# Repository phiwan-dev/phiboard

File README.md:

# phiboard
in progress, currently in the prototype phase...

# Third-Party Assets
### KiCad Symbols
The following Assets are from a third-party. Their original license still applies.
- Altium ISP1807-LR symbol in [`board/libraries/ISP1807-LR_Footprint.SchLib`](board/libraries/ISP1807-LR_Footprint.SchLib)
from the [manufacturers website](https://www.insightsip.com/products/bluetooth-le-modules/isp1807). There is no mention of a license.
- Kicad ISP1807-edit symbol in [`board/libraries/nordic-lib-kicad-isp1807.kicad_sym`](board/libraries/nordic-lib-kicad-isp1807.kicad_sym)
modified but based on the manufacturers symbol. Modifications follow this projects license (CERN-OHL-P-2.0).
- Kicad Nordic PMIC symbols in [`board/libraries/nordic-lib-kicad-npm.kicad_sym`](board/libraries/nordic-lib-kicad-npm.kicad_sym)
from https://github.com/hlord2000/nordic-lib-kicad using the CERN-OHL-P-2.0 license.
### KiCad Footprints
- Altium ISP1807-LR footprint in [`board/libraries/ISP1807-LR_Footprint.PcbLib`](board/libraries/ISP1807-LR_Footprint.PcbLib)
from the [manufacturers website](https://www.insightsip.com/products/bluetooth-le-modules/isp1807). There is no mention of a license.
- Kicad ISP1807-edit footprint in [`board/libraries/nordic-lib-kicad-isp1807.pretty`](board/libraries/nordic-lib-kicad-isp1807.pretty)
modified but based on the manufacturers symbol. Modifications follow this projects license (CERN-OHL-P-2.0).

<!-- ## Goals -->
<!-- - fully reversible pcb including hotswap sockets, MCU, OLED screen -->
<!-- - wireless using the XIAO BLE as MCU -->
<!-- - low profile (choc kailh) and thin PCB + components -->
<!-- - no visible screws from the top -->
<!-- - no visible seams from the top -->
<!-- - custom graphics and silk screen -->
<!-- - super easy, local zmk development -->

<!-- # Manual additions after Ergogen -->
<!-- Ergogen is used to generate most parts of the PCB. From within the ergogen folder, this can be done using: -->
<!-- ``` -->
<!-- ergogen . && cp output/pcbs/pcb.kicad_pcb ../kicad-prj/ -->
<!-- ``` -->
<!-- However, various smaller modifications as well as the reversible OLED and silkscreen graphics are placed manually by hand. -->
<!-- It is likely that this could be done through ergogen as well, feel free to fork and adjust my config. -->
<!-- All modifications are listed in here: -->
<!-- - Removed silksceens from diodes and modified silksceen for the battery pads. Be careful with this, as it make messing up the diode configuration very easy! -->
<!-- - Wired up MCU and keys in a reversible fashion -->
<!-- - Included reversible OLED --> 
<!-- - Put on silkscreens on front [`porsche-front-big.kicad_mod`](./kicad-prj/graphics.pretty/porsche-front-big.kicad_mod) and back [`porsche-back-big.kicad_mod`](./kicad-prj/graphics.pretty/porsche-back-big.kicad_mod) -->

<!-- # Customize Graphics -->
<!-- In [graphics](./kicad-prj/graphics/) you can find the source images used in this project. -->
<!-- There are two types of graphics. -->
<!-- ### Silkscreen -->
<!-- The silksceen uses the porsche images. -->
<!-- To use a different image you have to open `kicad > image converter`. -->
<!-- In here you can load your desired image, choose an output size and threshold and save it as footprint on F.Silkscreen. -->
<!-- In order for KiCad to detect your custom footprints, you have to save them to a folder with the extension `.pretty` like in [`kicad-prj/graphics.pretty/`](./kicad-prj/graphics.pretty/). -->
<!-- Lastly you need to tell KiCad where to find your footprints. -->
<!-- If you decide to use my project and its `graphics.pretty` folder then KiCad should automatically pick it up through the `fp-lib-table`. -->
<!-- Else, you can specify your `.pretty` path in `Preferences > Manage Footprint Libraries... > Project Specific Libraries`. -->
<!-- ### Solder Images -->
<!-- In the palm of the hand there is a little empty space on the PCB which I decided to use with images which are printed on there using solder. -->
<!-- I got the idea from [this video](https://www.youtube.com/watch?v=ohu4tZ4qov8). -->
<!-- Here is the workflow to put your own images on there: -->
<!-- You will most likely have a .png or .jpg image, which needs to be transformed to .svg. -->
<!-- For this you can use popular online tools like [convertio.co](https://convertio.co/). -->
<!-- Optionally you can try to optimize your svg using [this website](https://optimize.svgomg.net/), although it didn't make much of a difference for me. -->
<!-- Next, we need to transform our svg into an array of points, for which i used [this website](https://shinao.github.io/PathToPoints/). -->
<!-- Lastly, you can replace the point array in [`ergogen/footprints/phi-caps`](./ergogen/footprints/phi-caps.js) for the front side or [`ergogen/footprints/phi-logo`](./ergogen/footprints/phi-logo.js) for the back side. -->

<!-- # Parts -->
<!-- 40 keys, 20 per side -->
<!-- - 40 choc kailh switches -->
<!-- - 40 choc kailh keycaps -->
<!-- - 40 choc hotswap sockets -->
<!-- - 40 smd diodes 1N4148 -->
<!-- - 2 xiao ble -->
<!-- - 2 oled 0.91 inch i2c (optional) -->
<!-- - 2 batteries 3.7v (optional, requres cable otherwise) -->

<!-- # Firmware -->
<!-- Usually ZMK is compiled throug a GitHub actions workflow. However, I prefer to use it locally using a docker devcontainer. The devcontainer is provided by the official ZMK project. -->

<!-- ## Setting up the ZMK docker toolchain -->
<!-- ```bash -->
<!-- nix develop     # or install devcontainer cli otherwise -->
<!-- cd <path-to-phiboard>/firmware -->
<!-- ./setup-zmk.sh  # this may take a while -->
<!-- ``` -->

<!-- ## Compiling the ZMK firmware -->
<!-- ```bash -->
<!-- nix develop     # or install devcontainer cli otherwise -->
<!-- cd <path-to-phiboard>/firmware -->
<!-- ./build.sh  # clean build, is needed the first time -->
<!-- ./build.sh --cached   # faster, if a build has been done before -->
<!-- # the firmware is now located at <path-to-phiboard>/firmware/(left|right).uf2 -->
<!-- ``` -->

<!-- ## Flashing the firmware -->
<!-- - connect mcu with pc -->
<!-- - double press the reset button -->
<!-- - the file explorer should now show a usb media -->
<!-- - copy the corresponding .uf2 firmware to the usb media -->
<!-- - it should now auto-eject and run the new firmware -->

<!-- ## Fighting with ZMK -->
<!-- - spend a lot of time on local toolchain and scripts -->
<!-- - other projects may have their config files in different places -->
<!-- - explain most important files which the user might want to change (and where) -->
<!-- - confusing, overwhelming (at first) -->
<!-- - flash reset firmware to fix problems -->
<!-- - dtsi is "weird" because of the way the matrix is connected (only on prototype) -->
<!-- - right overlay columns are reversed because its mirrored but pcb is non-mirrored -->
<!-- - main half controls layers of secondary half -> perhaps need to flash both sides for keymap to take new changes -->
<!-- - displays have close to 0 documentation at all -->

<!-- # Soldering -->
<!-- - watch a solder intro video if you dont know what you are doing -->
<!-- - the second half will be better -->
<!-- - put solder on the pads, then heat the pads and press components in -->
<!-- - if possible, test connectivity from mcu to front pads -->
<!-- - care for diode direction (on prototype) -->

<!-- # Future fixes (from prototype) -->
<!-- - key spacing? -->
<!-- - different display -->

<!-- # Thanks -->
<!-- - to https://github.com/MvEerd/ergogen/tree/mveerd for ergogen -->
<!-- - to https://flatfootfox.com/ergogen-introduction/ for teaching ergogen -->
<!-- - to https://github.com/Pipshag/goosekb for inspiration on ergogen and zmk -->
<!-- - to https://www.youtube.com/watch?v=ohu4tZ4qov8 for finally making me follow through -->
<!-- - and many, many more! -->

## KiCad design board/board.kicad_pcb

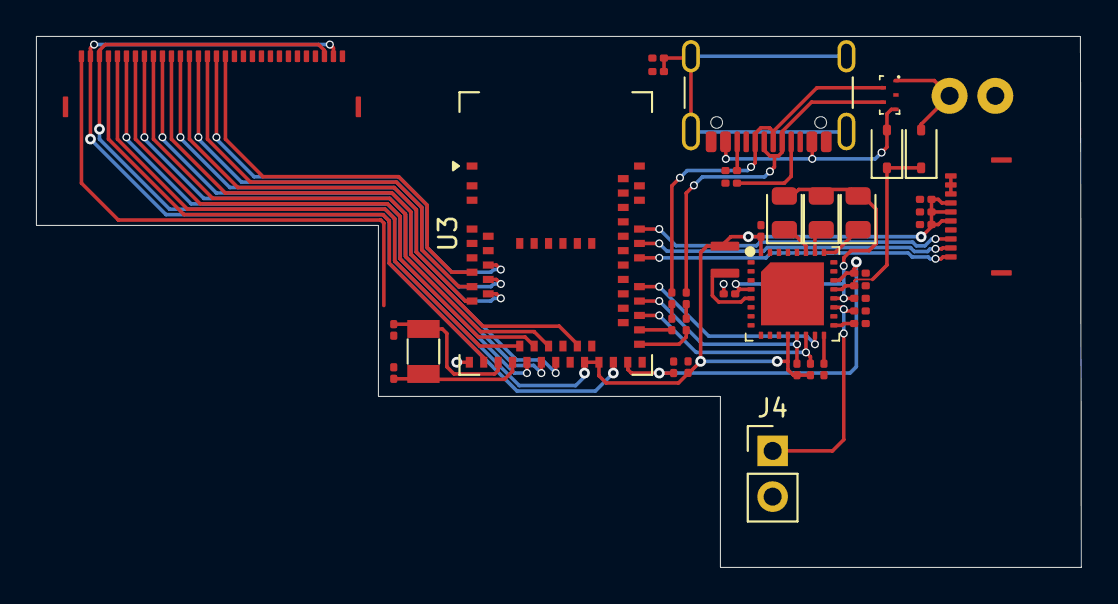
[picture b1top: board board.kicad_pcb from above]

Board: 2 copper layers, 58.1 x 29.5 mm, 41 parts (1 on the bottom side), 55 nets.

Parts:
C2: 10nF; C_0201_0603Metric
C3, C4, C12, C14: 1uF; C_0201_0603Metric
C6: 470pF; C_0201_0603Metric
C7, C8: 12.5pF; C_0201_0603Metric
C9, C10, C15, C16, C17: 10uF; C_0201_0603Metric
C13: 2.2uF; C_0201_0603Metric
D3, D4: D_Schottky; D_SOD-323
D6, D7, D8: LED; LED_0805_2012Metric
J2: Conn_01x10; THD_0510-10CL-GF
J3: Conn_01x06; swd_pad
J4: Conn_01x02; PinHeader_1x02_P2.54mm_Vertical
J7: Conn_01x30; THD_0510-30CL-GF
J8: USB_C_Receptacle_USB2.0_16P; USB_C_Receptacle_GCT_USB4105-xx-A_16P_TopMnt_Horizontal
J9: Conn_01x02; magnetic connector 01x02P
L1: 2.2uH; L_0806_2016Metric
R4, R14: 5.1kR; R_0201_0603Metric
R5, R12, R13: 10kR; R_0201_0603Metric
R6, R7, R8, R9: 10R; R_0201_0603Metric
R10: 0R; R_0201_0603Metric
R11: 250-500kR; R_0201_0603Metric
U2: nPM1300-QEAA; nordic_npm1300-QEAA_qfn
U3: MDBT50Q-P1MV2; Raytac_MDBT50Q
U4: TVS_Array; DFN2010
Y1: 32k Hz; Crystal_SMD_3215-2Pin_3.2x1.5mm

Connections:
+1V8: J7.2, J7.29, U3.31 (DCCH)
+3V3: C3.1, C4.1, C6.1, C10.2, C17.1, J2.5, J2.6, J2.7, J3.2, J7.3, J7.28, L1.2, R12.1, R13.1, U2.12 (VDDIO), U2.32 (VOUT2), U3.28 (VDD), U3.30 (VDDH)
GND: C2.1, C3.2, C4.2, C6.2, C7.2, C8.2, C9.2, C10.1, C12.1, C13.2, C14.2, C15.2, C16.2, C17.2, J2.4, J2.8, J2.9, J2.10, J3.6, J4.2, J7.1, J7.30, J8.A1 (GND), J8.A12 (GND), J8.B1 (GND), J8.B12 (GND), J9.2, R4.1, R5.1, R10.1, R11.1, R14.1, U2.6 (PVSS2), U2.18 (NTC), U2.33 (AVSS), U3.1 (GND), U3.2 (GND), U3.15 (GND), U3.33 (GND), U3.55 (GND), U4.2 (GND)
unnamed: D3.2 (A), J8.A4 (VBUS), J8.A9 (VBUS), J8.B4 (VBUS), J8.B9 (VBUS), U4.3
unnamed: D4.2 (A), J9.1, U4.1
unnamed: D6.1 (K), U2.25 (LED0)
unnamed: D7.1 (K), U2.26 (LED1)
unnamed: D8.1 (K), U2.27 (LED2)
unnamed: J8.A5 (CC1), R4.2
unnamed: J8.B5 (CC2), R14.2
unnamed: C2.2, J8.S1 (SHIELD), R5.2
unnamed: R6.1, R7.2
unnamed: R8.1, R9.2
unnamed: L1.1, U2.5 (SW2)
unnamed: R10.2, U2.17 (VSET1)
unnamed: R11.2, U2.16 (VSET2)
unnamed: R8.2, U3.35 (D+)
unnamed: R6.2, U3.34 (D-)
unnamed: C8.1, U3.17 (P0.00), Y1.1
unnamed: C7.1, U3.18 (P0.01), Y1.2
key1: J7.4, U3.16 (P0.27)
key2: J7.5, U3.19 (P0.26)
key3: J7.6, U3.20 (P0.04)
key4: J7.7, U3.21 (P0.05)
key5: J7.8, U3.22 (P0.06)
key6: J7.9, U3.23 (P0.07)
key7: J7.10, U3.24 (P0.08)
key8: J7.11, U3.27 (P0.11)
key9: J7.12, U3.13 (P0.28)
key10: J7.13, U3.14 (P0.30)
key11: J7.14, U3.11 (P0.02)
key12: J7.15, U3.12 (P0.31)
key13: J7.16, U3.9 (P0.03)
key14: J7.17, U3.10 (P0.29)
key18: J7.21, U3.42 (P0.19)
key19: J7.22, U3.43 (P0.21)
key20: J7.23, U3.45 (P0.23)
key21: J7.24, U3.49 (P0.25)
key22: J7.25, U3.52 (P0.09)
key23: J7.26, U3.54 (P0.10)
nreset: J3.5, U3.40 (P0.18)
scl: R13.2, U2.14 (SCL), U3.37 (P0.13)
sclk: J2.1, U3.44 (P0.20)
scs: J2.3, U3.48 (P0.24)
sda: R12.2, U2.13 (SDA), U3.39 (P0.15)
shphld: U2.15 (SHPHLD), U3.41 (P0.17)
si: J2.2, U3.46 (P0.22)
swd_clk: J3.4, U3.53 (SWDCLK)
swd_data: J3.3, U3.51 (SWDIO)
usbd+: J8.A6 (D+), J8.B6 (D+), R9.1, U4.5
usbd-: J8.A7 (D-), J8.B7 (D-), R7.1, U4.4
vbat: C13.1, J4.1, U2.19 (VBAT)
vbus: C9.1, C14.1, U2.22 (VBUSOUT), U3.32 (VBUS)
vbus_raw: C12.2, D3.1 (K), D4.1 (K), U2.21 (VBUS)
vsys: C15.1, C16.1, D6.2 (A), D7.2 (A), D8.2 (A), U2.4 (PVDD), U2.20 (VSYS)

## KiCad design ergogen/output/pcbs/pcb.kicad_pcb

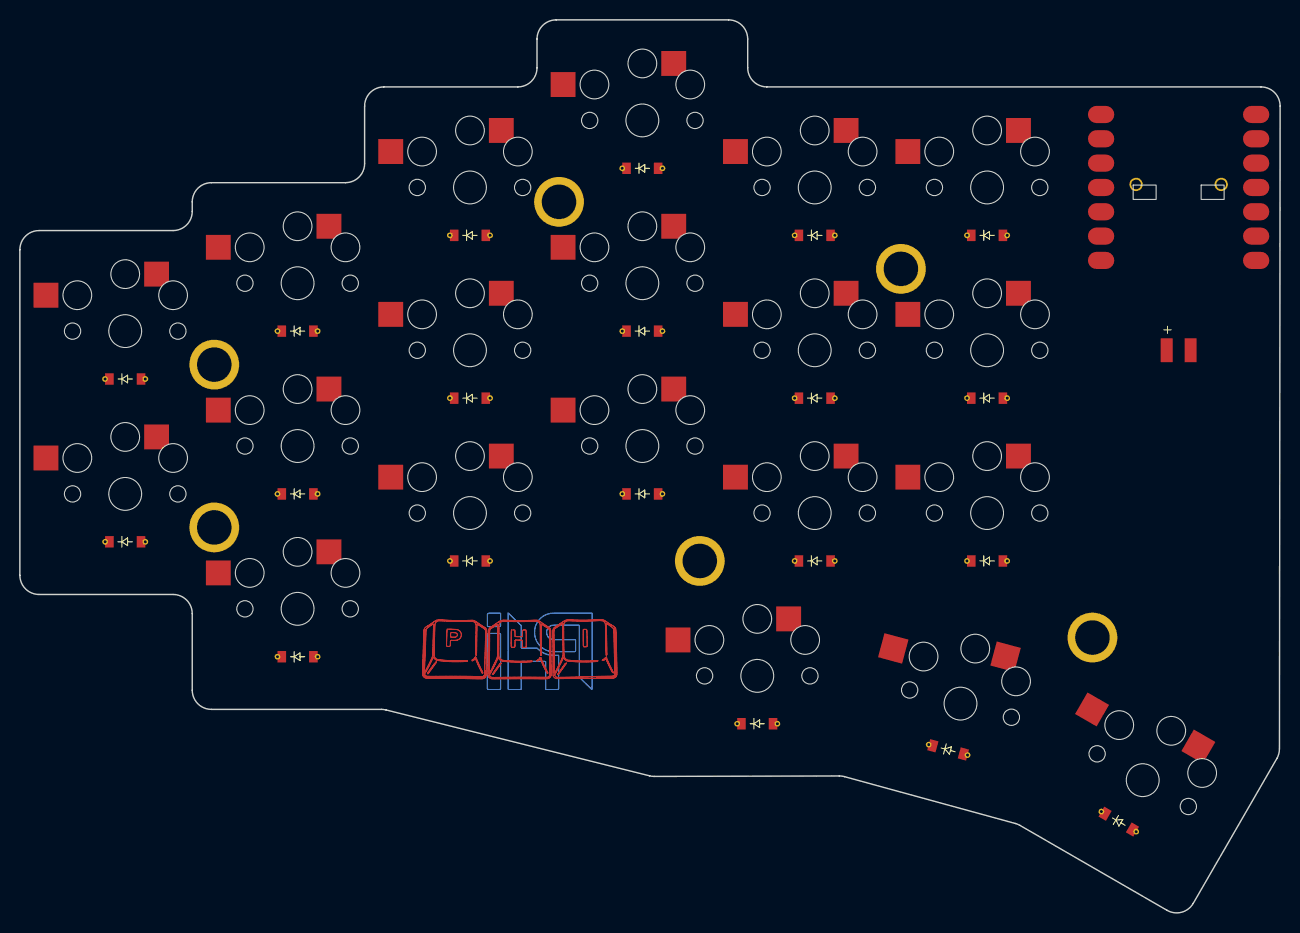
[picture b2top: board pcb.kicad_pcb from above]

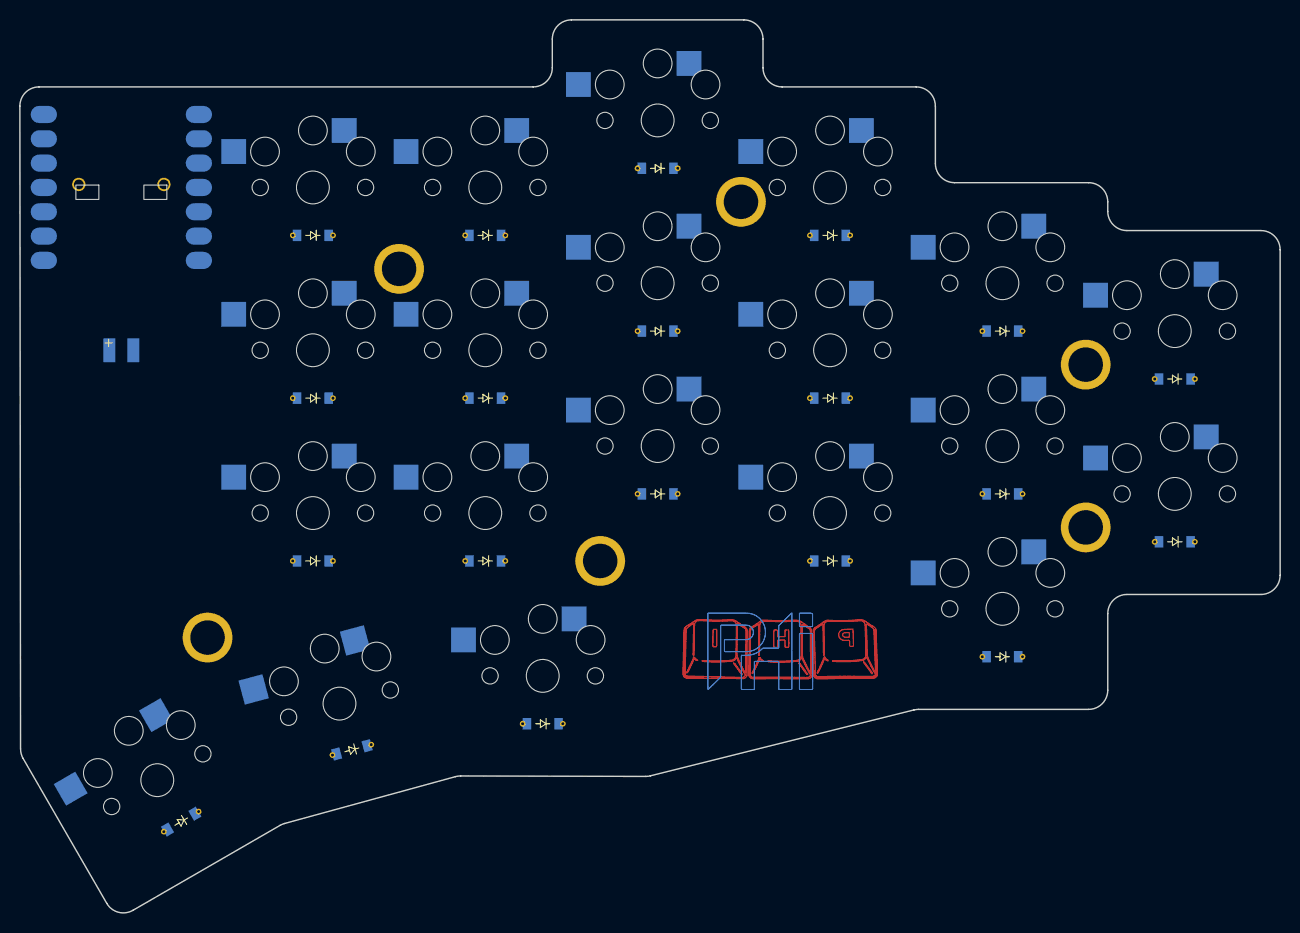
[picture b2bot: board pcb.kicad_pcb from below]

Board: 2 copper layers, 131.6 x 93.2 mm, 48 parts (20 on the bottom side), 31 nets, no tracks yet.

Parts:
Di1, Di2, Di3, Di4, Di5, Di6, Di7, Di8, Di9, Di10, Di11, Di12, Di13, Di14, Di15, Di16, Di17, Di18, Di19, Di20: D_SOD-123
H1, H2, H3, H4, H5, H6: mounting_hole
MCU1: xiao-ble-smd-reversible
PAD1: pads
S1, S2, S3, S4, S5, S6, S7, S8, S9, S10, S11, S12, S13, S14, S15, S16, S17, S18, S19, S20: PG1350

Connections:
BAT+: MCU1.19, PAD1.1, PAD1.2
GND: MCU1.13, PAD1.1, PAD1.2
cindex: MCU1.8, S12.1, S13.1, S14.1, S19.1
cinner: MCU1.7, S15.1, S16.1, S17.1, S20.1
cmiddle: MCU1.9, S9.1, S10.1, S11.1, S18.1
cpinky: MCU1.11, S2.1, S3.1, S4.1, S5.1
cring: MCU1.10, S1.1, S6.1, S7.1, S8.1
index_bottom: Di12.2, S12.2
index_home: Di13.2, S13.2
index_top: Di14.2, S14.2
inner_bottom: Di15.2, S15.2
inner_home: Di16.2, S16.2
inner_top: Di17.2, S17.2
left_cluster: Di18.2, S18.2
middle_bottom: Di9.2, S9.2
middle_cluster: Di19.2, S19.2
middle_home: Di10.2, S10.2
middle_top: Di11.2, S11.2
outer_home: Di1.2, S1.2
outer_top: Di2.2, S2.2
pinky_bottom: Di3.2, S3.2
pinky_home: Di4.2, S4.2
pinky_top: Di5.2, S5.2
rbottom: Di3.1, Di6.1, Di9.1, Di12.1, Di15.1, MCU1.3
rhome: Di4.1, Di7.1, Di10.1, Di13.1, Di16.1, MCU1.2
right_cluster: Di20.2, S20.2
ring_bottom: Di6.2, S6.2
ring_home: Di7.2, S7.2
ring_top: Di8.2, S8.2
rthumbs: Di1.1, Di2.1, Di18.1, Di19.1, Di20.1, MCU1.4
rtop: Di5.1, Di8.1, Di11.1, Di14.1, Di17.1, MCU1.1

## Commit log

2025-05-23 dev: init
2025-05-23 dev: add units
2025-05-23 dev: add main matrix
2025-05-23 dev: add thumb cluster
2025-06-04 dev: add flake for dev shell
2025-06-04 dev: enable nix-direnv
2025-06-04 dev: add board outline
2025-06-06 dev: add more tooling to flake
2025-06-06 fix: remove mirror attribute in favor of reversable pcb
2025-06-06 dev: add pcb with reverse hotswap choc switches
2025-06-07 dev: add diodes with custom footprint
2025-06-07 dev: add mcu to ble
2025-06-07 dev: add readme with parts list
2025-06-07 dev: add kicad project for pcb editing
2025-06-07 dev: add column and row nets to keys
2025-06-07 dev: add battery pads
2025-06-07 dev: add screw points and mounting points
2025-06-09 dev: add small pcb graphics
2025-06-09 dev: add source graphics used for pcb
2025-06-09 dev: add pcb graphic footprints
2025-06-09 dev: add output files
2025-06-09 dev: remove diode silkscreens
2025-06-09 dev: wired up mcu pads on pcb
2025-06-09 dev: wire up key matrix
2025-06-09 dev: include reversible oled screen
2025-06-10 fix: remove reset cutouts from xiao ble
2025-06-10 dev: add kicad outputs
2025-06-10 fix: update readme
2025-06-10 fix: tidy up config
2025-06-10 dev: add LICENSE
2025-07-11 dev: init zmk files
2025-07-19 dev: add zmk docker tutorial to readme
2025-07-20 fix: restructure project into distinct ergogen, kicad and zmk folders
2025-07-20 fix: use goosekb zmk config as starting point for firmware
2025-07-20 zmk: renamed goose to phiboard
2025-07-20 zmk: remove sensors
2025-07-20 docs: reflect changes in readme
2025-07-20 zmk: add setup script
2025-07-20 zmk: add build script
2025-07-20 docs: add script usage to readme
2025-07-20 fix: rename goose folder to phiwan
2025-07-21 zmk: refine build and setup script
2025-07-21 fix: adapt zmk pins
2025-07-22 zmk: add outer keys to dtsi
2025-07-22 zmk: start with keymap (base layer)
2025-07-22 zmk: add bt keys
2025-07-22 zmk: add setting_reset firmware
2025-07-22 fix: zmk right side mirrored columns
2025-07-22 zmk: change main and peripheral side
2025-07-23 fix: zmk base layer modifiers
2025-07-24 zmk: add special character layer
2025-07-24 zmk: add number and F-key layer
2025-07-24 zmk: add naviagion and umlaut layer
2025-07-24 zmk: add homerow combos
2025-08-03 zmk: add screen to right half
2025-08-03 zmk: remove encoder from conf
2025-08-03 zmk: add screen to left half
2025-08-03 fix: update flake and gitignore
2025-08-25 zmk: fix display configuration to not glitch anymore
2025-08-30 zmk: qol build script improvement
2025-12-01 zmk: add key wakeup from deepsleep
2025-12-02 flake: move to 25.11
2025-12-02 flake: start for new board
2025-12-03 ergogen: sort pin order alphanumerically
2025-12-03 zmk: remove unused defines
2025-12-03 zmk: remove unused behaviors
2025-12-03 zmk: add bt profile buttons
2025-12-04 zmk: add symbol explanation
2025-12-05 docs: readme add zmk section
2025-12-05 docs: readme add soldering section
2025-12-05 docs: readme add future fixes section
2025-12-05 docs: reset readme
2026-01-10 ergogen: remove files because they are unused now
2026-01-10 other: remove prototype kicad files
2026-01-10 other: remove unused project files
2026-01-10 other: change license for future work
2026-01-10 board: start kicad project
2026-01-11 zmk: prepare move to new repository
2026-01-12 docs: prepare for third party assets from different licenses
2026-01-12 board: add manufacturer isp1807 symbol
2026-01-12 board: start own isp1807 symbol
2026-01-13 board: reorganize symbol libraries
2026-01-13 board: add npm symbol library
2026-01-13 board: start schematic
2026-01-14 board: pmic add usb
2026-01-14 board: pmic add led and gpio
2026-01-14 board: pmic add twi
2026-01-14 baord: pmic add buck1
2026-01-14 board: pmic add buck2 and disable ldo1+2
2026-01-14 board: pmic add battery management
2026-01-15 board: display add cable
2026-01-15 board: display add power delivery net
2026-01-15 board: sch display add extmode and extcomin
2026-01-15 board: sch display add disp signal
2026-01-15 board: sch board to board connector
2026-01-15 board: sch internal usb connector
2026-01-15 board: sch tidy up and battery connector
2026-01-15 board: sch add mcu
2026-01-15 board: sch mcu connect power
2026-01-16 board: sch configure vusb
2026-01-16 board: sch configure swd
2026-01-16 board: sch mcu gpio
2026-01-16 board: pcb init
2026-01-17 board: add manufacturer ISP1807 footprint
2026-01-17 board: start isp1807 footprint in own library
2026-02-02 board: add gitignore files from board directory
2026-02-02 board: create custom DF40C footprint for project
2026-02-02 board: create custom XUNPU FPC recepticle footprint
2026-02-03 board: remove center pads from isp1807
2026-02-03 board: try different footprint placements
2026-02-03 board: outline key matrix in pcb
2026-02-03 board: change outline to flat 19 mm spacing (instead of 19.05 mm)
2026-02-11 board: start rough footprint placement
2026-02-11 board: add normal voltage mode to raytac module
2026-02-11 board: start move to raytac MDBT50Q-1MV2 instead of isp1807
2026-02-11 board: add data lines to raytac module
2026-02-11 board: sch add external 32k crystal
2026-02-12 board: sch move power circuitry from pmic to raytac module
2026-02-13 board: sch add spi to nrf
2026-02-13 board: sch remove unused isp1807
2026-02-14 board: sch change board connector to 1x30 instead of 1x20 to include power lanes
2026-02-16 board: configure bom plugin
2026-02-16 board: sch add footprints for R and C and for C LCSC PN number
2026-02-16 board: sch add led footprint plus lcsc pn
2026-02-16 board: sch add r lcsc pn
2026-02-17 board: sch create own npm1300 symbol
2026-02-18 board: sch create own phiboard library for custom symbols
2026-02-19 board: sch move to power circuit to new symbol
2026-02-20 board: pcb fix naming and pad number
2026-02-20 board: pcb add inductor 0806 footprint
2026-02-21 board: sch L add lcsc pn and footprint
2026-02-22 board: pcb add swd pad footprint
2026-02-22 board: sch crystal add lcsc pn and footprint
2026-02-22 board: sch fix swd connect with new footprint
2026-02-22 board: sch tidy up display connector
2026-02-22 board: pcb add 1x10 ffc connector footprint
2026-02-22 board: sch assign display connector new ffc connector footprint and lcsc pn
2026-02-23 board: pcb add npm1300 qfn footprint
2026-02-24 board: pcb add 1x30 ffc connector footprint
2026-02-24 board: sch assign footprint to board to board connector
2026-02-24 board: sch add footprint and lcsc pn to npm1300
2026-02-24 board: pcb magnetic connector footprint
2026-02-25 board: sch add battery pad
2026-02-25 board: sch add usb c to magnet adapter
2026-02-26 board: sch add usb circuit
2026-02-27 board: sch add emi protection
2026-02-27 board: pcb rough footprint placement
2026-02-27 board: pcb remove unused footprints
2026-02-27 board: pcb adjust text in footprints
2026-02-27 board: sch add usb receptacle lcsc pn and footprint
2026-02-27 board: pcb add smb footprint
2026-02-27 board: sch add esd protection
2026-02-28 board: sch add mounting pin to ffc connectors
2026-02-28 board: pcb re-link footprints
2026-02-28 board: pcb add i2c and fix spi
2026-02-28 board: sch add keys
2026-02-28 board: sch add shphld
2026-02-28 board: sch display correct capacitor configuration
2026-03-01 board: sch fix remaining part numbers and key placement
2026-03-01 board: pcb remove text for visibility
2026-03-02 board: sch remove unpopulated components from schematic
2026-03-03 board: pcb move components to approximate location
2026-03-04 board: sch add new esd protection symbol
2026-03-04 board: pcb add dfn2010 footprint
2026-03-04 board: pcb fix courtyard and orientation silkscreen for footprints
2026-03-05 board: pcb implement schematic changes in pcb
2026-03-05 board: pcb route pmic power
2026-03-05 board: sch fix tvs diode array symbol
2026-03-05 board: sch change tvs diode array to BDFN2010A054R
2026-03-05 board: sch fix usb cc1/2 pins to 5.1kR
2026-03-05 board: sch change schottky diodes to smaller footprint
2026-03-06 board: pcb route pmic i2c
2026-03-06 board: pcb route pmic led
2026-03-06 board: pcb route vbus_raw
2026-03-06 board: pcb route cc and vbus
2026-03-07 board: pcb route pmic buck converter
2026-03-07 board: pcb route crystal
2026-03-07 board: pcb route usbd+-
2026-03-07 board: pcb move components and traces extending over the edge
2026-03-07 board: pcb add edge cuts
2026-03-07 board: pcb route (most of) 3.3V
2026-03-08 board: pcb add usb shield grounding
2026-03-08 board: pcb change edge constraint to fit jlcpcb
2026-03-08 board: sch change case grounding resistor from 300kR to 10kR
2026-03-08 board: pcb route display spi
2026-03-08 board: pcb optimize routing
2026-03-08 board: pcb route shphld
2026-03-09 board: pcb route bottom front keys
2026-03-09 board: sch change board2board power order
2026-03-09 board: pcb reroute bottom front keys with changed power order
2026-03-09 board: pcb route bottom back keys
2026-03-09 board: pcb route left key pins
2026-03-09 board: sch change left key pins assignment to better match connector
